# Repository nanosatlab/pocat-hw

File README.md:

# 3CatNXT PocketQube — Hardware

Hardware repository for the IEEE GRSS PocketQube built at the [NanoSat Lab (UPC)](https://nanosatlab.upc.edu/).

It holds the complete electrical and mechanical design of the satellite: KiCad projects for every
PCB in the stack, the SolidWorks/STEP assembly of the full spacecraft, the deployment mechanisms,
and the ground/mechanical support equipment used to integrate and test it.

This repository contains **design data only** — there is nothing to build or run. Flight and
ground software live elsewhere, as does the PL3 payload hardware
([nanosatlab/pocat-rfi-5g](https://github.com/nanosatlab/pocat-rfi-5g)).

---

## Repository layout

| Path | What it is |
|---|---|
| `pq_eps/` | Electrical Power Subsystem |
| `pq_obc_comms/` | On-Board Computer + COMMS transceiver |
| `pq_adcs/` | Attitude Determination and Control System |
| `pq_pl1/` | Payload 1 interface board |
| `pq_pl2/` | Payload 2 — L-band receiver |
| `pq_topboard/` | +Z face board |
| `pq_botboard/` | −Z face board |
| `pq_latboard/` | Lateral (side) face board |
| `pq_ymag_board/` | +Y magnetorquer board |
| `pq_botnotsobot/` | Deployment-switch / slider board |
| `pq_egse/` | EGSE — electrical ground support equipment breakout |
| `assembly/` | SolidWorks + STEP mechanical assembly of the whole satellite |
| `Vitrina_PQ/` | Display case (acrylic showcase) for the engineering model |

Each KiCad project directory typically contains the `.kicad_sch` / `.kicad_pcb` / `.kicad_pro`
triplet, an exported `.step` for mechanical integration, and a `production/` folder with the IPC
netlist and (where fabricated) Gerbers. Directories suffixed `_old` are superseded revisions kept
for traceability; `pq_pl2/Imports/` holds the original Altium design that PL2 was migrated from.

---

## The boards

The satellite is a stack of 40 × 40 mm boards held between structural face boards that also carry
the solar cells and thermal sensors.

### Stack boards (40 × 40 mm)

**`pq_eps` — Electrical Power Subsystem** · 4-layer, 1.6 mm

Solar energy harvesting through **SPV1040** MPPT boost converters, battery charging and
power-path management by an **LTC4040**, coulomb counting via a **DS2782** fuel gauge, and
regulated rails from an **ISL9120** buck-boost. Carries the kill-switch logic that gates the
main regulator, plus the antenna burn-wire release (`BURNCOMMS`) and per-rail enables for the
ADCS and payloads. Battery is a single Li-ion **LP14430** cell.

**`pq_obc_comms` — On-Board Computer & COMMS** · 4-layer, 1.6 mm

**STM32L476RGT6** microcontroller with a 32 MHz TCXO and a 32.768 kHz RTC crystal, paired with a
**SX1262** sub-GHz LoRa transceiver. RF front end uses a **BGS12PL6** antenna switch out to U.FL
and MS-156C test connectors. The STM32CubeMX pin configuration lives alongside the project in
`STM32L476RG_config/STM32L476RG_config.ioc`, and an interactive BOM is generated at
`pq_obc_comms/bom/ibom.html`.

**`pq_adcs` — Attitude Determination & Control** · 6-layer, 1.6 mm

Sensing from an **IIM-42652** 6-axis IMU and an **MMC5983MA** magnetometer, with sun-sensor
conditioning through **LPV542** op-amps and a **TMUX1108** analog multiplexer.

Two revisions are tracked:
- `PQ_ADCS/` — original design, magnetorquer coils driven by a **BD2606MVV**.
- `PQ_ADCS_HBridge/` — current revision, redesigned around **DRV8214** H-bridge drivers. The
  vendor-supplied symbol, footprint and STEP for the DRV8214 are vendored in
  `PQ_ADCS_HBridge/DRV8214RTER/`.

**`pq_pl2` — L-band receiver payload** · 4-layer, 1.58 mm

Full receive chain: **BFCG162W** LNA → **LEE2-6+** gain stage → **MAX2121** direct-conversion
tuner, with an **LT5537** RF power detector for level monitoring and an **LT3048** ultra-low-noise
LDO feeding the RF section. Clocked by an **ECS-TXO-2016MV** TCXO; MS-156C and U.FL connectors
provide antenna and test access.

**`pq_pl1` — Payload 1 interface** · 2-layer, 1.6 mm

Passive interface/adapter board exposing the stack connector to the PL1 experiment.

### Face and structural boards

**`pq_topboard` / `pq_botboard` / `pq_latboard`** · 2-, 6- and 6-layer respectively

These form the outer faces of the cube. They mount **SLCD-61N8** solar cells and **TCN75A**
digital temperature sensors, and route the harness into the stack. The bottom board additionally
carries **TPS7A7001/7002** LDOs, and the lateral board brings out coaxial connectors for the
deployable antenna. Face boards are 2 mm thick because they are structural.

**`pq_ymag_board`** · 6-layer, 2 mm, 45 × 45 mm

+Y magnetorquer — an air-core coil etched into the PCB, driven from the ADCS board.

**`pq_botnotsobot`** · 2-layer, 1.6 mm, 64 × 58 mm

Slider board carrying the **D2FLA** deployment/kill switches that hold the satellite inert inside
the deployer.

**`pq_egse`** · 6-layer

Electrical Ground Support Equipment. A large breakout fixture that fans every stack connector out
to 0.1" headers so subsystems can be probed, powered and stimulated individually on the bench.
Fabrication Gerbers and drill files are checked in under `pq_egse/manufacturing/`.

---

## Mechanical assembly

`assembly/` is the SolidWorks model of the integrated spacecraft. The top-level assemblies are:

- `ieee_grss_pocketqube.SLDASM` — the full satellite.
- `ieee_grss_pocketqube_beta antena.SLDASM` — variant with the deployed antenna configuration.

Supporting content is organised by subsystem — `eps/`, `adcs/`, `obc&comms/`, `payloads/`,
`structure/`, `lateral/`, `bottom/`, `slider/` — and each PCB folder carries the board as both a
`.step` and a `.SLDPRT`, together with the Edge_Cuts and silkscreen DXF/SVG exports used to keep
the mechanical model in sync with the electrical design.

Of note:

- **`assembly/lateral/antena-deployment/`** — the COMMS tape-spring antenna and its burn-wire
  release: turret, pivot, spring, clip and the resistor that cuts the restraint.
- **`assembly/Lband_Deployment_Mechanism/`** — deployment mechanism for the L-band payload
  antenna (`Lband3d_2res_v7.2.SLDASM`), with its own board and antenna sub-assemblies and a
  `STEP_files/` export set.
- **`assembly/payloads/pl3/`** — RFI-5G payload structure (antenna, supports, SMP interface).
  Mechanical only — the PL3 electrical design lives in its own repository,
  [nanosatlab/pocat-rfi-5g](https://github.com/nanosatlab/pocat-rfi-5g).
- **`assembly/MGSE_Assembly/`** — Mechanical Ground Support Equipment: the jigs and supports used
  to hold the satellite during integration.
- **`assembly/structure/`** — chassis parts plus the screw, nut and spacer library (M2/M3 ISO).

---

## Working with this repository

**Tools.** KiCad 7 or newer is required; the EPS and ADCS H-Bridge projects have been saved with a
more recent file format (`20260206`) than the rest of the stack, so opening them in an older KiCad
will fail. Mechanical files are SolidWorks, with STEP exports provided for anyone without it.

**Exports are checked in on purpose.** STEP files, Edge_Cuts/silkscreen DXFs and `production/`
netlists are tracked so that mechanical integration and manufacturing can proceed without
re-running KiCad. If you change a board outline or a connector position, re-export the STEP and
DXF and commit them in the same change — otherwise the mechanical assembly silently drifts out of
date.

**What is ignored.** `.gitignore` excludes KiCad backups, autosaves, lock files, netlists, and
generated BOM `.csv`/`.xml`. Note that it also ignores `production/` and `*-backups/` directories
by default; the ones present in the repository were committed before those rules were added and
remain tracked.

**Branching.** Work happens on per-subsystem branches (`eps_updated`, `adcs_hbridge_revision`,
`Lateral_and_bottom_connectors`, …) which are merged into `main` once the revision passes review.
Binary CAD files do not merge — coordinate before two people edit the same board.

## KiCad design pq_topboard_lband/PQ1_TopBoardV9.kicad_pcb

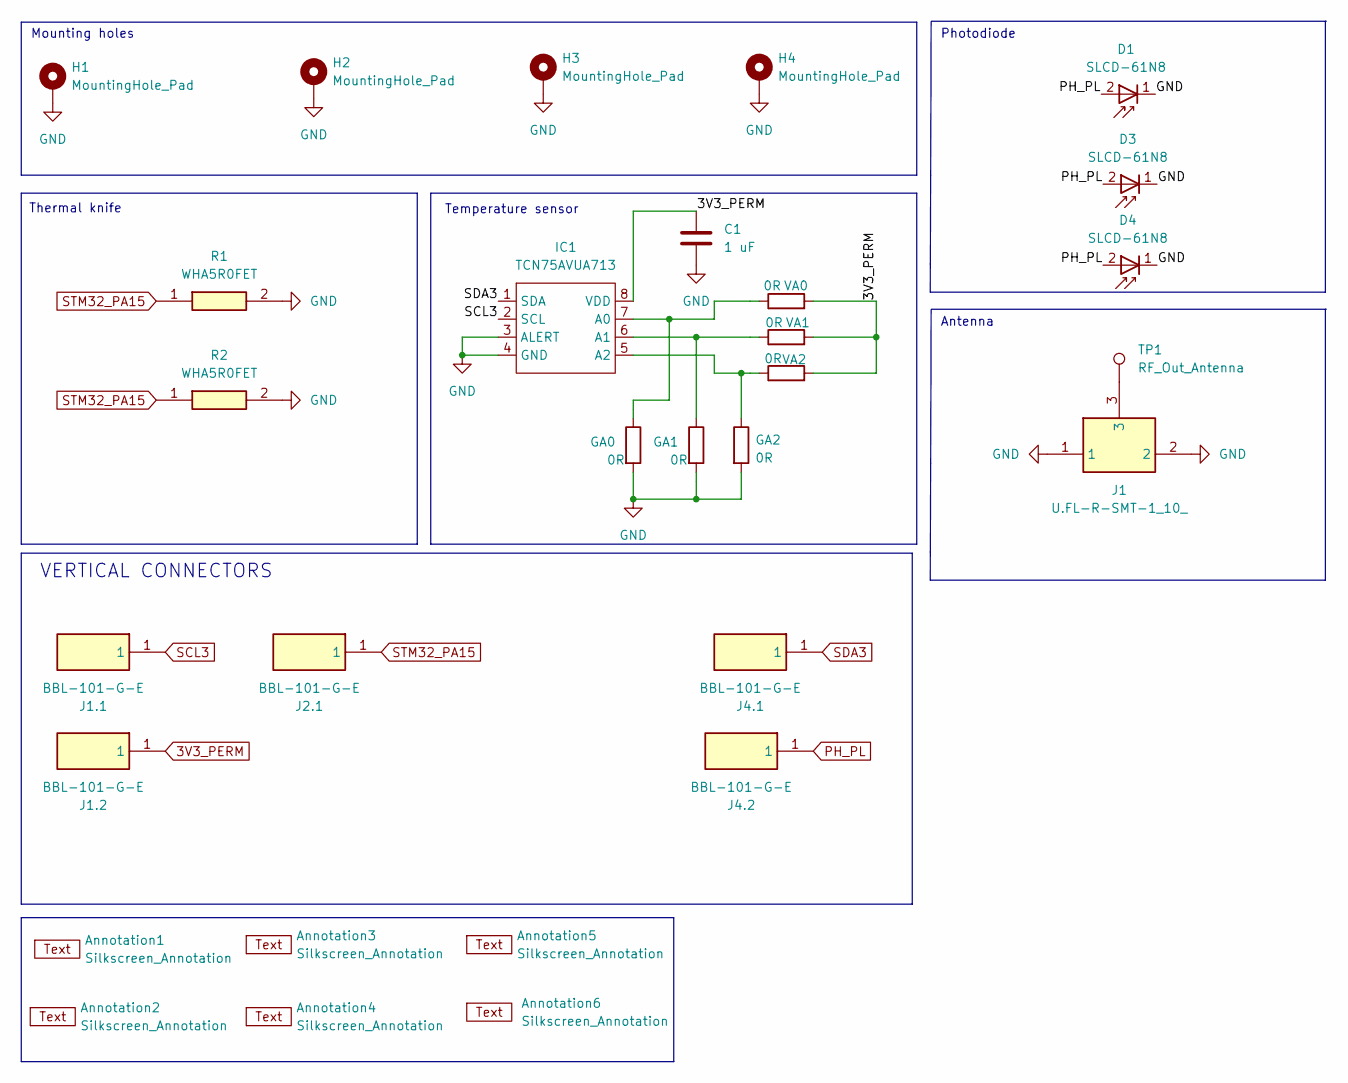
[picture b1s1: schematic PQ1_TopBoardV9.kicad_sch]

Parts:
Annotation1: Silkscreen_Annotation; IEEE_logo
Annotation2: Silkscreen_Annotation; GRSS
Annotation3: Silkscreen_Annotation; NSL_long
Annotation4: Silkscreen_Annotation; Telecos
Annotation5: Silkscreen_Annotation; UPC_positiu
Annotation6: Silkscreen_Annotation; NSL_Lektron
C1: 1 uF; C_0603_1608Metric; Manufacturer Part Numbe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 GRM188R72A104KA35J
D1, D3, D4: SLCD-61N8; Manufacturer Part Numbe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 SLCD-61N8
GA0, GA1, GA2: 0R; R_0805_2012Metric; Manufacturer Part Numbe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 CRCW08055K00JNTA
H1, H2, H3, H4: MountingHole_Pad; MountingHole_3.2mm_M3_ISO14580_Pad; Manufacturer Part Numbe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 N/A
IC1: TCN75AVUA713; TCN75AVOA; Manufacturer Part Numbe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 TCN75AVOA
J1: U.FL-R-SMT-1_10_; Mouser Part Number 798-U.FL-R-SMT-110
J1.1, J1.2, J2.1, J4.1, J4.2: BBL-101-G-E; BBL-101-Y-X; Mouser Part Number 200-BBL101GE
R1, R2: WHA5R0FET; RESAD1524W60L508D254; Mouser Part Number 588-WHA5R0FET
TP1: RF_Out_Antenna; TestPoint_Keystone_5015_Micro_Mini
VA0, VA1, VA2: 0R; R_0805_2012Metric; Manufacturer Part Numbe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 CRCW08055K00JNTA

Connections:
3V3_PERM: C1.1, IC1.8 (VDD), J1.2.1 (1_1), VA0.2, VA1.2, VA2.2
GND: C1.2, D1.1, D3.1, D4.1, GA0.2, GA1.2, GA2.2, H1.1 (1_1), H2.1 (1_1), H3.1 (1_1), H4.1 (1_1), IC1.3 (ALERT), IC1.4 (GND), J1.1, J1.2, R1.2, R2.2
unnamed: GA0.1, IC1.7 (A0), VA0.1
unnamed: GA1.1, IC1.6 (A1), VA1.1
unnamed: GA2.1, IC1.5 (A2), VA2.1
unnamed: J1.3, TP1.1 (1_1)
PH_PL: D1.2, D3.2, D4.2, J4.2.1 (1_1)
SCL3: IC1.2 (SCL), J1.1.1 (1_1)
SDA3: IC1.1 (SDA), J4.1.1 (1_1)
STM32_PA15: J2.1.1 (1_1), R1.1, R2.1

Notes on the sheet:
Photodiode
VERTICAL CONNECTORS
Thermal knife
Mounting holes
Antenna
Temperature sensor

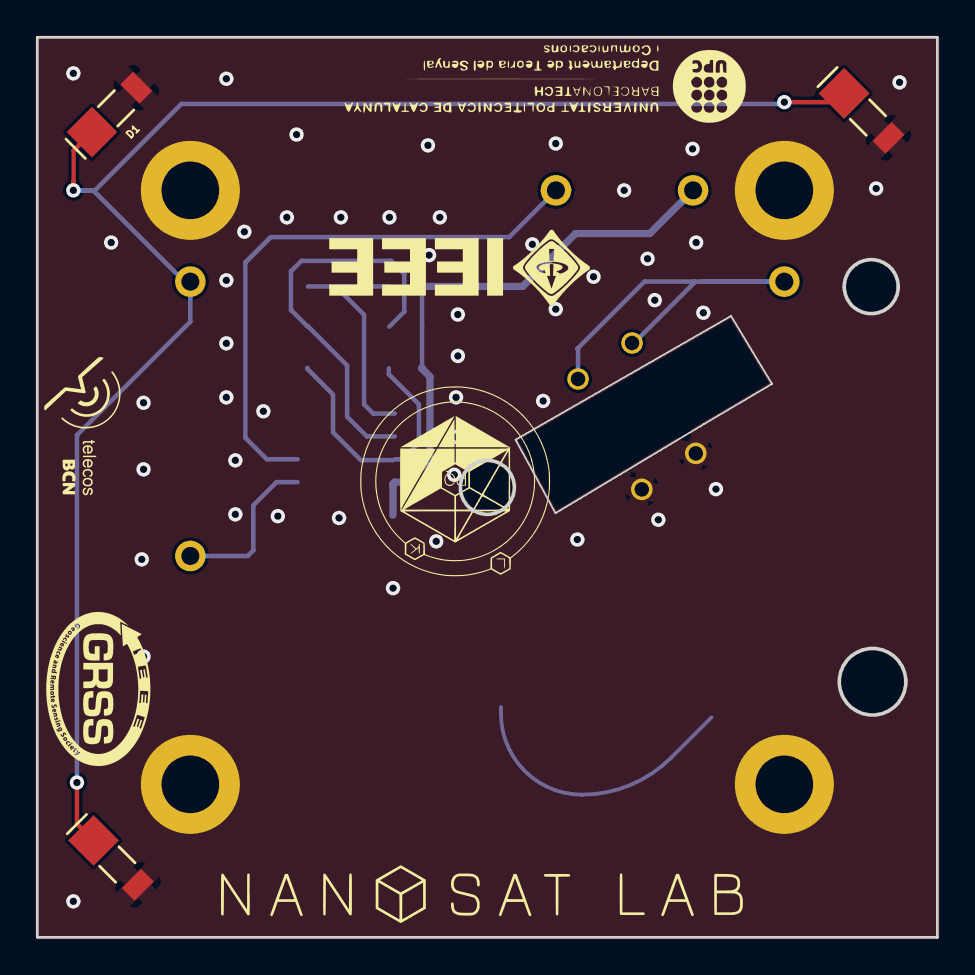
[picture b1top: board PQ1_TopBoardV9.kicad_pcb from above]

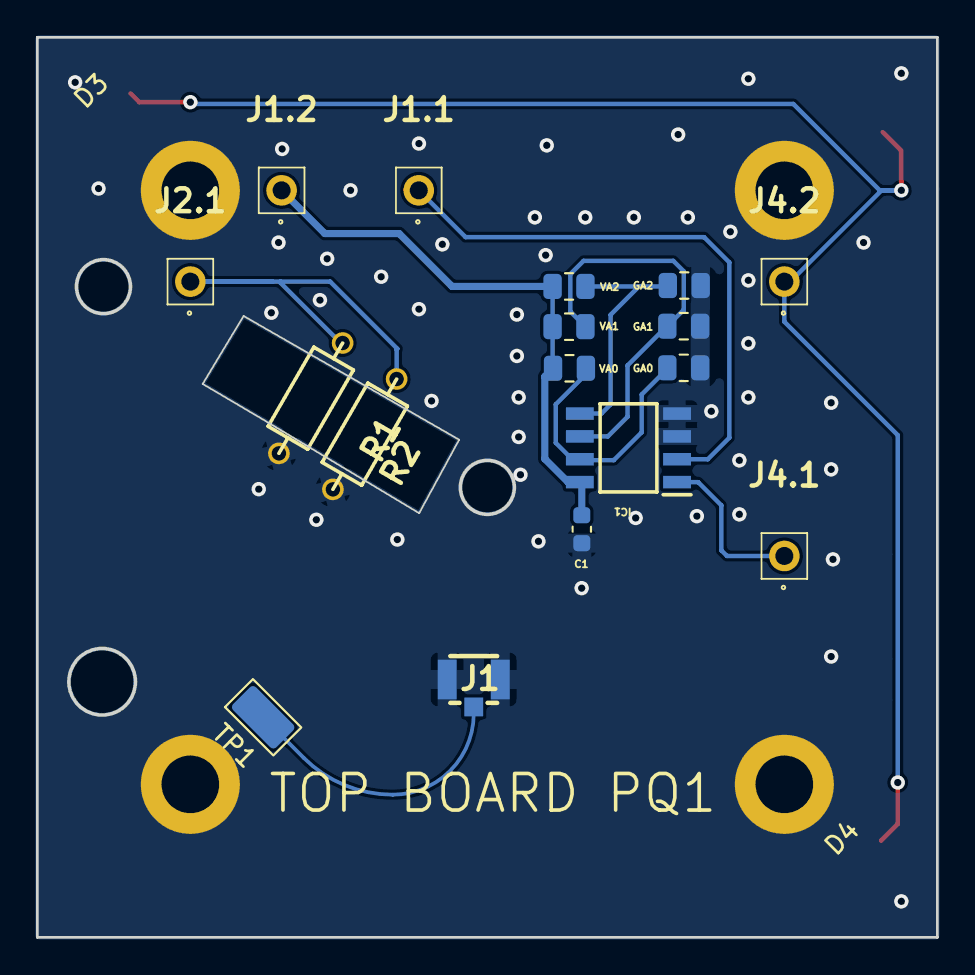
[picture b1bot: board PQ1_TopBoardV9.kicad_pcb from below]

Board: 2 copper layers, 50.0 x 50.0 mm, 30 parts (17 on the bottom side), 10 nets.

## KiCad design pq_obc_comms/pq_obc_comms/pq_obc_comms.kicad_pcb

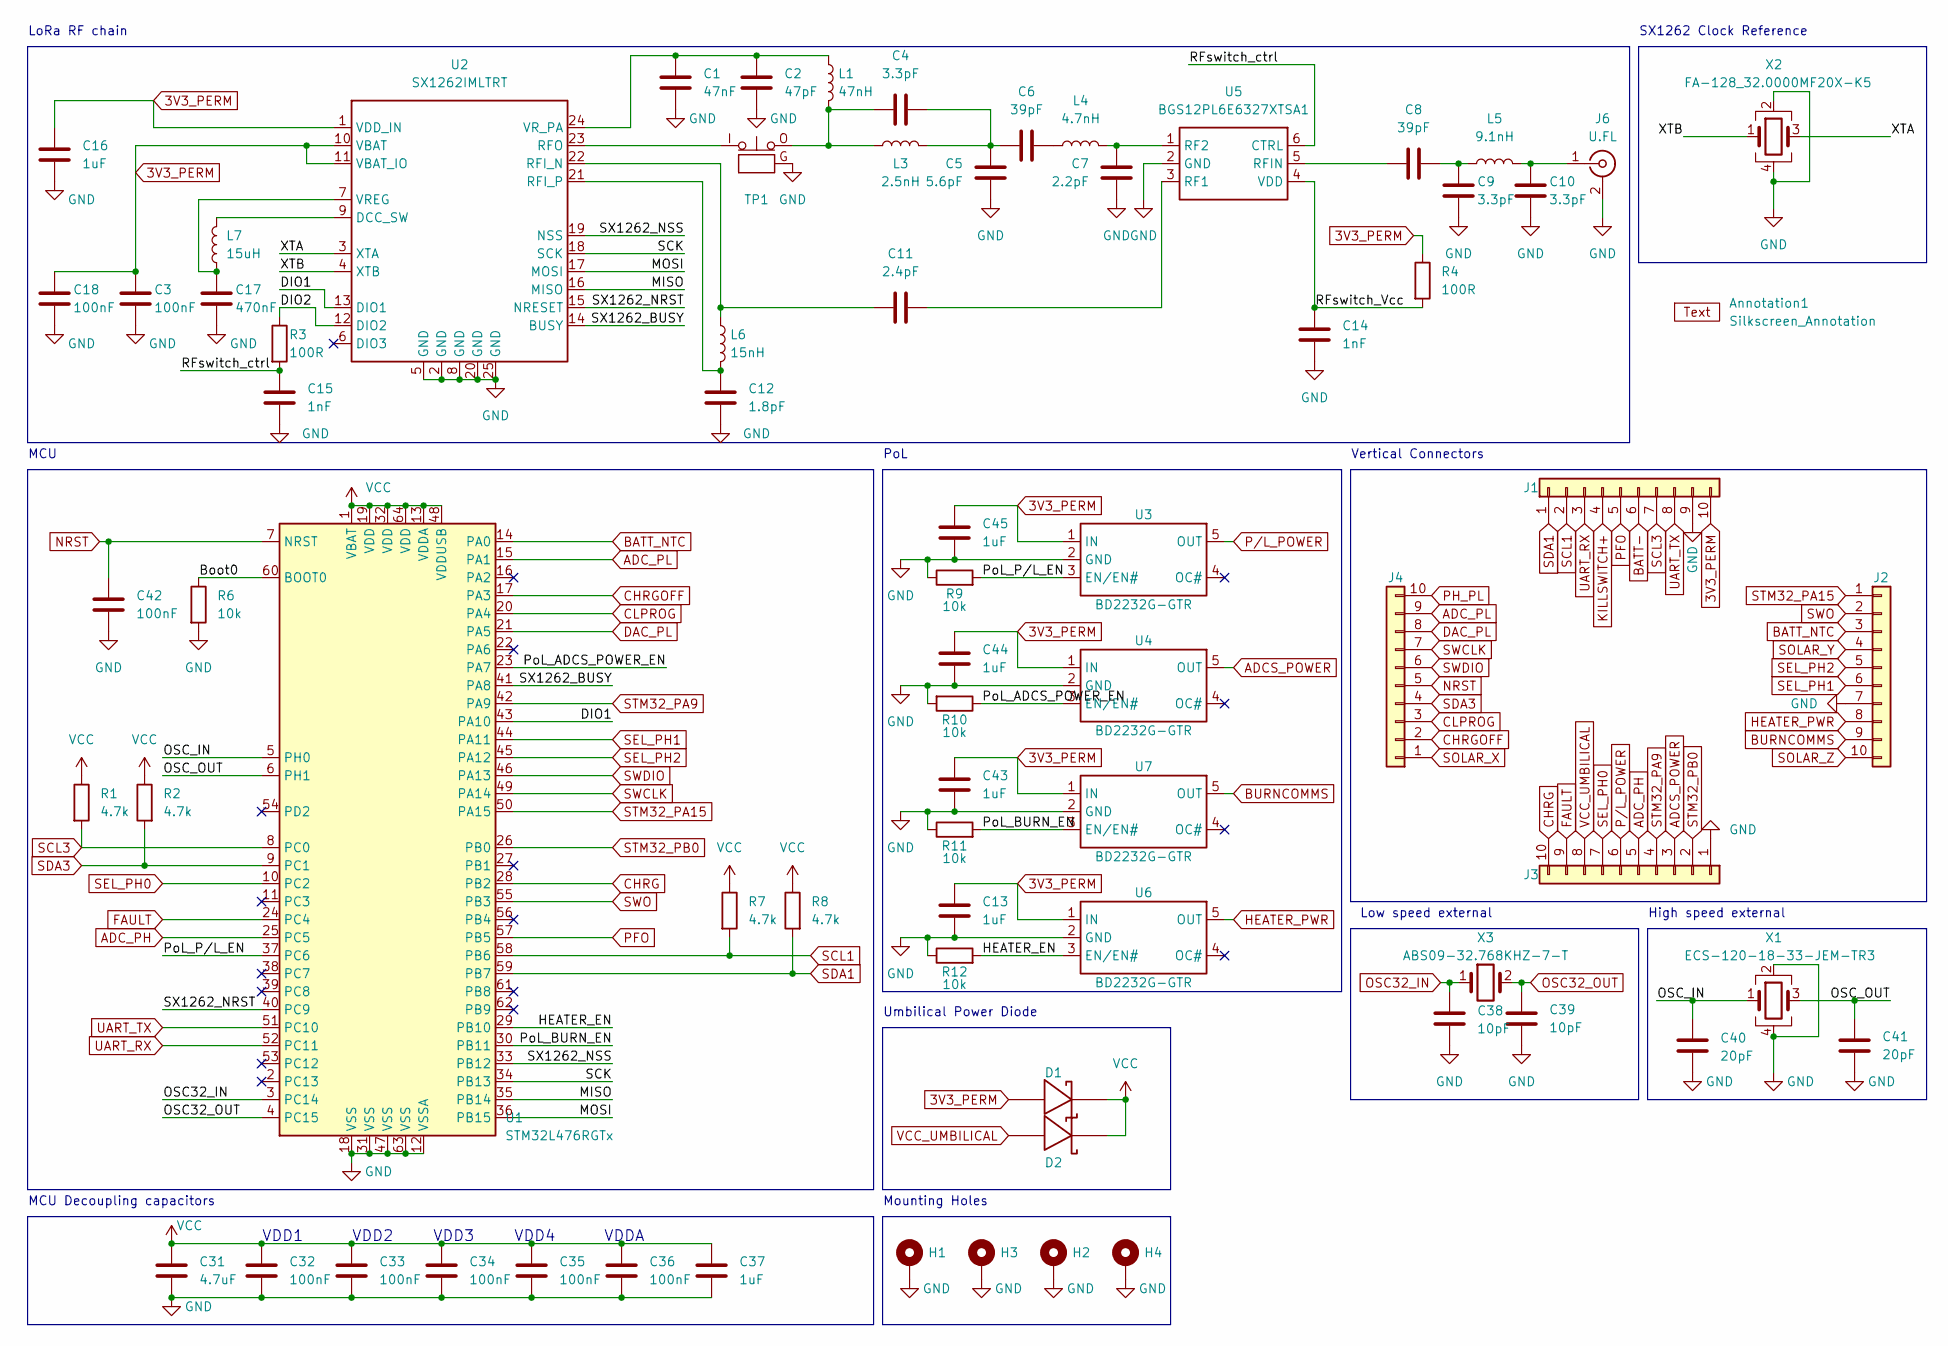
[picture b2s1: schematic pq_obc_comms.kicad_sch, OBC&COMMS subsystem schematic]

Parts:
Annotation1: Silkscreen_Annotation; Bike
C1: 47nF; C_0402_1005Metric; Manufacturer Part Numbe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 GRM155R71C473KA01J
C2: 47pF; C_0402_1005Metric; Manufacturer Part Numbe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 GJM1555C1H470JB01J
C3, C18, C32, C33, C34, C35, C36, C42: 100nF; C_0603_1608Metric; Manufacturer Part Numbe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 GRM188R72A104KA35J
C4, C9, C10: 3.3pF; C_0402_1005Metric; Manufacturer Part Numbe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 600L3R3BT200T
C5: 5.6pF; C_0402_1005Metric; Manufacturer Part Numbe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 600L5R6BTN200T
C6, C8: 39pF; C_0402_1005Metric; Manufacturer Part Numbe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 GJM1555C1H390FB01D
C7: 2.2pF; C_0402_1005Metric; Manufacturer Part Numbe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 600L2R2BT200T
C11: 2.4pF; C_0402_1005Metric; Manufacturer Part Numbe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 600L2R4BW200T
C12: 1.8pF; C_0402_1005Metric; Manufacturer Part Numbe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 600L1R8BW200T
C13, C16, C37, C43, C44, C45: 1uF; C_0603_1608Metric; Manufacturer Part Numbe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 GRM188R61A105KA61D
C14, C15: 1nF; C_0603_1608Metric; Manufacturer Part Numbe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 0603B102K500CT
C17: 470nF; C_0603_1608Metric; Manufacturer Part Numbe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 GRM188R7YA474KE05D
C31: 4.7uF; C_0603_1608Metric; Manufacturer Part Numbe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 GRT188R61E475KE13D
C38, C39: 10pF; C_0603_1608Metric; Manufacturer Part Numbe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 06035A100GAT2A
C40, C41: 20pF; C_0603_1608Metric; Manufacturer Part Numbe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 GCM1885C2A200JA16D
D1, D2: type="D" model="RBS1LAM40ATR" lib=""; RBS1LAM40ATR_Schottky; Manufacturer Part Numbe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 RBS1LAM40ATR
H1, H2, H3, H4: MountingHole_Pad; MountingHole_3.2mm_M3_Pad
J1, J2, J3, J4: Conn_01x10; SLW-110-01; Manufacturer Part Numbe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 CES-110-01-T-S
J6: U.FL; U.FL_Hirose_U.FL-R-SMT-1_Vertical; Manufacturer Part Numbe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 U.FL-R-SMT-1(10)
L1: 47nH; L_0402_1005Metric; Manufacturer Part Numbe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 0402DC-47NXGRW
L3: 2.5nH; L_0402_1005Metric; Manufacturer Part Numbe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 LQW15AN2N5B00D
L4: 4.7nH; L_0402_1005Metric; Manufacturer Part Numbe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 0402DC-4N7XGRW
L5: 9.1nH; L_0402_1005Metric; Manufacturer Part Numbe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 LQW15AN9N1G8ZD
L6: 15nH; L_0402_1005Metric; Manufacturer Part Numbe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 LQW15AN15NH00D
L7: 15uH; L_0805_2012Metric; Manufacturer Part Numbe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 LQM21DN150M70L
R1, R2, R7, R8: 4.7k; R_0603_1608Metric; Manufacturer Part Numbe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 CRCW06034K70JNEAC
R3, R4: 100R; R_0603_1608Metric; Manufacturer Part Numbe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 RC0603JR-07100RL
R6, R9, R10, R11, R12: 10k; R_0402_1005Metric; Manufacturer Part Numbe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 CRCW040220K0FKEDC
TP1: CoaxialSwitch_Testpoint; CoaxialSwitch_Hirose_MS-156C3_Horizontal; Manufacturer Part Numbe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 MS-156C3(20)
U1: STM32L476RGTx; LQFP-64_10x10mm_P0.5mm; Manufacturer Part Numbe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 STM32L476RGT6
U2: SX1262IMLTRT; QFN-24-1EP_4x4mm_P0.5mm_EP2.6x2.6mm; Manufacturer Part Numbe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 SX1262IMLTRT
U3, U4, U6, U7: BD2232G-GTR; SOT-23-5; Manufacturer Part Numbe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 BD2232G-GTR
U5: BGS12PL6E6327XTSA1; PG-TSLP-6-4; Manufacturer Part Numbe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 BGS12PL6E6327XTSA1
X1: ECS-120-18-33-JEM-TR3; ECS-120-18-33; Manufacturer Part Numbe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 ECS-120-18-33-JEM-TR3
X2: FA-128_32.0000MF20X-K5; EPSON_FA128; Manufacturer Part Numbe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 FA-128 32.0000MF20X-K5
X3: ABS09-32.768KHZ-7-T; ABS09; Manufacturer Part Numbe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 ABS09-32.768KHZ-7-T

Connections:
3V3_PERM: C3.1, C13.1, C16.1, C18.1, C43.1, C44.1, C45.2, D1.2, J1.10, R4.1, U2.1 (VDD_IN), U2.10 (VBAT), U2.11 (VBAT_IO), U3.1 (IN), U4.1 (IN), U6.1 (IN), U7.1 (IN)
/Boot0: R6.1, U1.60 (BOOT0)
/DIO1: U1.43 (PA10), U2.13 (DIO1)
/DIO2: R3.1, U2.12 (DIO2)
/HEATER_EN: R12.2, U1.29 (PB10), U6.3 (EN/EN#)
/MISO: U1.35 (PB14), U2.16 (MISO)
/MOSI: U1.36 (PB15), U2.17 (MOSI)
/OSC_IN: C40.1, U1.5 (PH0), X1.1
/OSC_OUT: C41.1, U1.6 (PH1), X1.3
/PoL_ADCS_POWER_EN: R10.1, U1.23 (PA7), U4.3 (EN/EN#)
/PoL_BURN_EN: R11.2, U1.30 (PB11), U7.3 (EN/EN#)
/PoL_P/L_EN: R9.2, U1.37 (PC6), U3.3 (EN/EN#)
/RFswitch_Vcc: C14.1, R4.2, U5.4 (VDD)
/RFswitch_ctrl: C15.1, R3.2, U5.6 (CTRL)
/SCK: U1.34 (PB13), U2.18 (SCK)
/SX1262_BUSY: U1.41 (PA8), U2.14 (BUSY)
/SX1262_NRST: U1.40 (PC9), U2.15 (NRESET)
/SX1262_NSS: U1.33 (PB12), U2.19 (NSS)
/XTA: U2.3 (XTA), X2.3
/XTB: U2.4 (XTB), X2.1
ADCS_POWER: J3.3, U4.5 (OUT)
ADC_PH: J3.5, U1.25 (PC5)
ADC_PL: J4.9, U1.15 (PA1)
BATT-: J1.6
BATT_NTC: J2.3, U1.14 (PA0)
BURNCOMMS: J2.9, U7.5 (OUT)
CHRG: J3.10, U1.28 (PB2)
CHRGOFF: J4.2, U1.17 (PA3)
CLPROG: J4.3, U1.20 (PA4)
DAC_PL: J4.8, U1.21 (PA5)
FAULT: J3.9, U1.24 (PC4)
GND: C1.2, C2.2, C3.2, C5.2, C7.2, C9.2, C10.2, C12.2, C13.2, C14.2, C15.2, C16.2, C17.2, C18.2, C31.2, C32.2, C33.2, C34.2, C35.2, C36.2, C37.2, C38.2, C39.2, C40.2, C41.2, C42.2, C43.2, C44.2, C45.1, H1.1 (1_1), H2.1 (1_1), H3.1 (1_1), H4.1 (1_1), J1.9, J2.7, J3.1, J6.2 (Ext), R6.2, R9.1, R10.2, R11.1, R12.1, TP1.G, U1.12 (VSSA), U1.18 (VSS), U1.31 (VSS), U1.47 (VSS), U1.63 (VSS), U2.2 (GND), U2.5 (GND), U2.8 (GND), U2.20 (GND), U2.25 (GND), U3.2 (GND), U4.2 (GND), U5.2 (GND), U6.2 (GND), U7.2 (GND), X1.2, X1.4, X2.2, X2.4
HEATER_PWR: J2.8, U6.5 (OUT)
KILLSWITCH+: J1.4
NRST: C42.1, J4.5, U1.7 (NRST)
unnamed: C4.1, L1.2, L3.1, TP1.O
unnamed: C4.2, C5.1, C6.1, L3.2
unnamed: C6.2, L4.1
unnamed: C8.2, C9.1, L5.1
unnamed: C10.1, J6.1 (In), L5.2
unnamed: L7.2, U2.9 (DCC_SW)
unnamed: C11.1, L6.1, U2.22 (RFI_N)
unnamed: C12.1, L6.2, U2.21 (RFI_P)
unnamed: TP1.I, U2.23 (RFO)
unnamed: C17.1, L7.1, U2.7 (VREG)
unnamed: C1.1, C2.1, L1.1, U2.24 (VR_PA)
unnamed: C11.2, U5.3 (RF1)
unnamed: C7.1, L4.2, U5.1 (RF2)
unnamed: C8.1, U5.5 (RFIN)
OSC32_IN: C38.1, U1.3 (PC14), X3.1
OSC32_OUT: C39.1, U1.4 (PC15), X3.2
PFO: J1.5, U1.57 (PB5)
PH_PL: J4.10
SCL1: J1.2, R7.2, U1.58 (PB6)
SCL3: J1.7, R1.2, U1.8 (PC0)
SDA1: J1.1, R8.2, U1.59 (PB7)
SDA3: J4.4, R2.2, U1.9 (PC1)
SEL_PH0: J3.7, U1.10 (PC2)
SEL_PH1: J2.6, U1.44 (PA11)
SEL_PH2: J2.5, U1.45 (PA12)
SOLAR_X: J4.1
SOLAR_Y: J2.4
SOLAR_Z: J2.10
STM32_PA9: J3.4, U1.42 (PA9)
STM32_PA15: J2.1, U1.50 (PA15)
STM32_PB0: J3.2, U1.26 (PB0)
SWCLK: J4.7, U1.49 (PA14)
SWDIO: J4.6, U1.46 (PA13)
SWO: J2.2, U1.55 (PB3)
UART_RX: J1.3, U1.52 (PC11)
UART_TX: J1.8, U1.51 (PC10)
VCC: C31.1, C32.1, C33.1, C34.1, C35.1, C36.1, C37.1, D1.1, D2.1, R1.1, R2.1, R7.1, R8.1, U1.1 (VBAT), U1.13 (VDDA), U1.19 (VDD), U1.32 (VDD), U1.48 (VDDUSB), U1.64 (VDD)
VCC_UMBILICAL: D2.2, J3.8

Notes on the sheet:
VDD2
MCU Decoupling capacitors
LoRa RF chain
SX1262 Clock Reference
Umbilical Power Diode
VDD1
Low speed external
Vertical Connectors
MCU
VDD3
VDDA
High speed external
Mounting Holes
VDD4
PoL

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
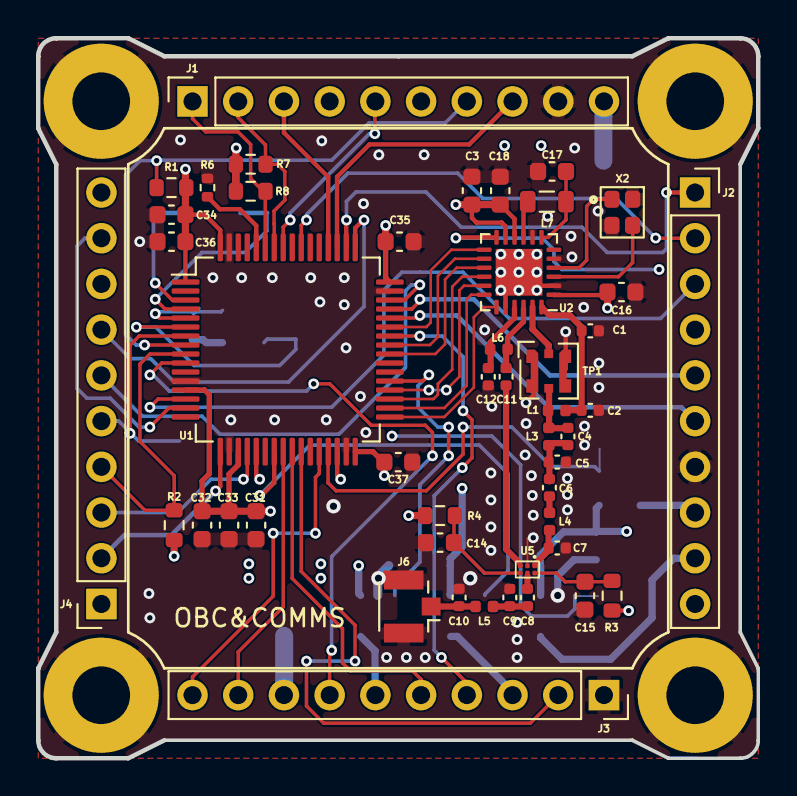
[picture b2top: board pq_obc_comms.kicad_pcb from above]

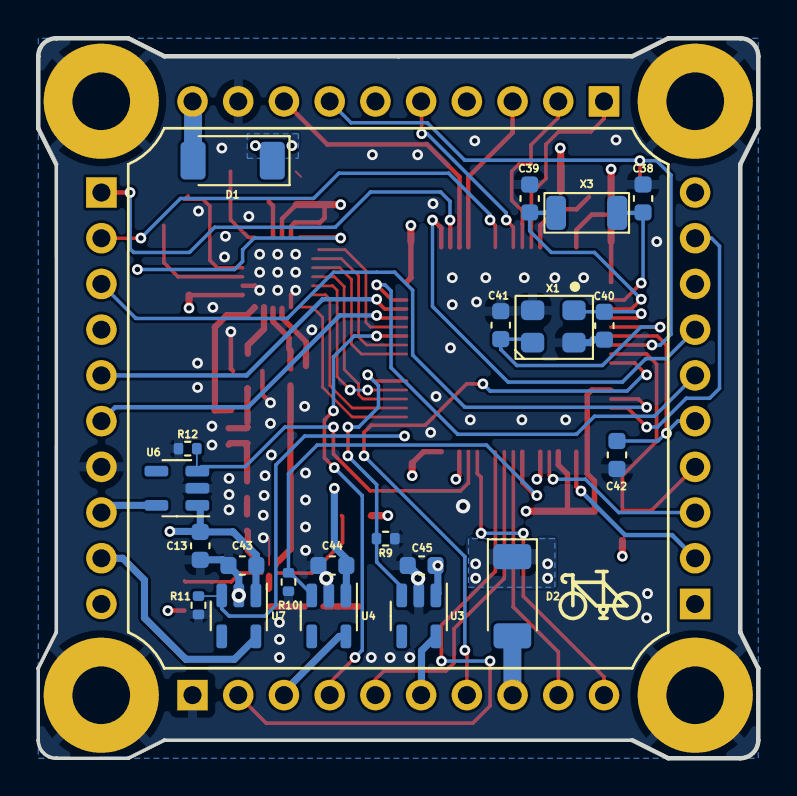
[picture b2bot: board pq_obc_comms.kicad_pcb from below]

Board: 4 copper layers, 40.0 x 40.0 mm, 73 parts (22 on the bottom side), 68 nets.

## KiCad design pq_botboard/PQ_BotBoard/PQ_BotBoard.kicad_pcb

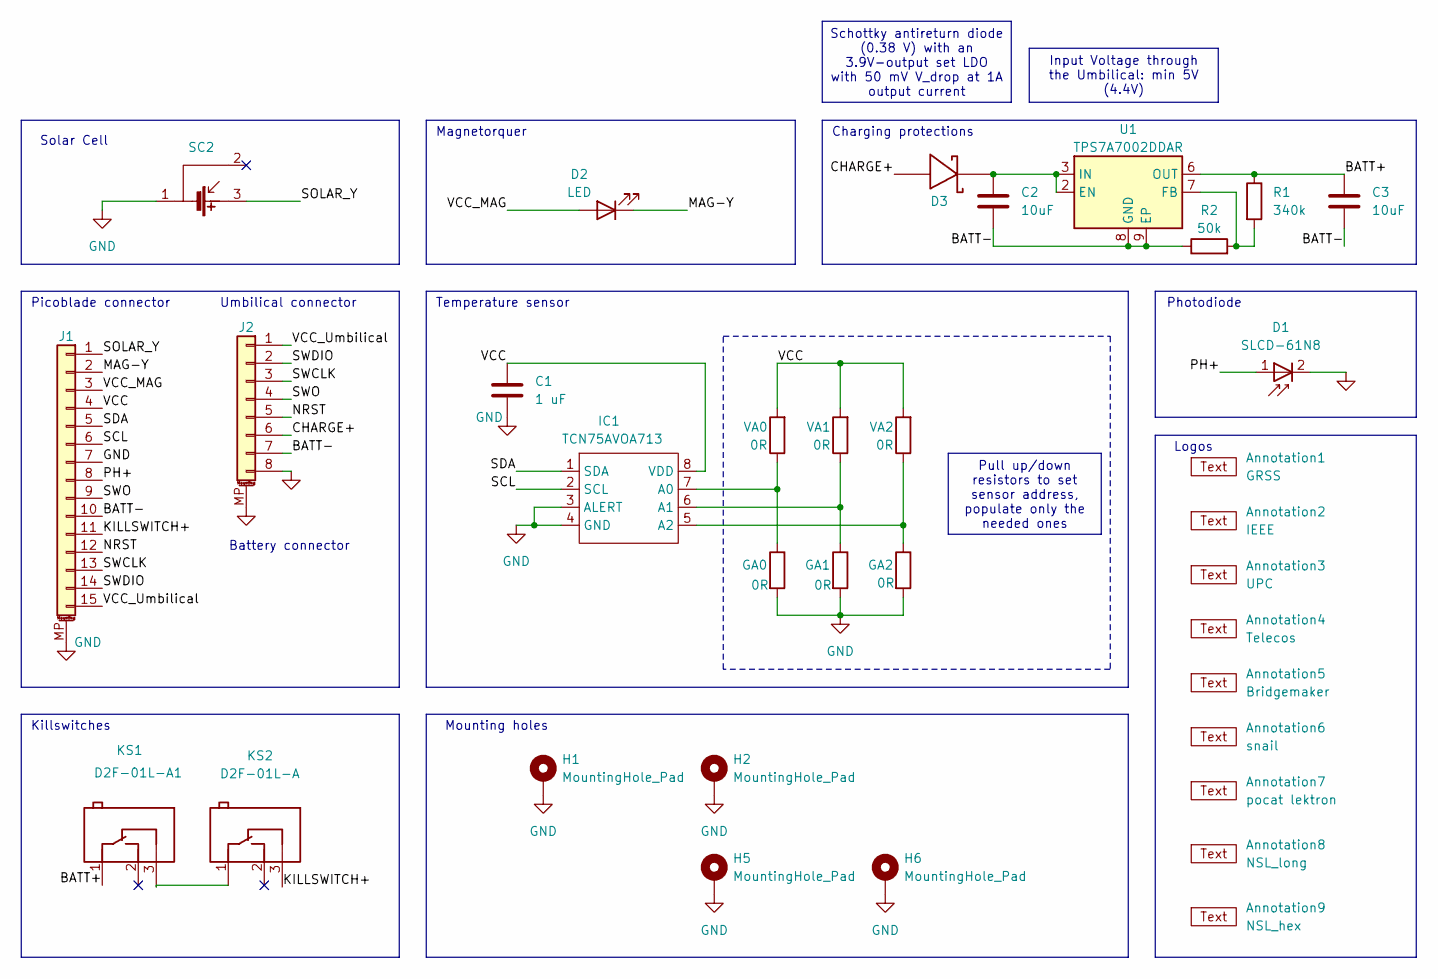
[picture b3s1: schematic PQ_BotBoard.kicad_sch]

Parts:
Annotation1: GRSS
Annotation2: IEEE; IEEE_logo
Annotation3: UPC; UPC_positiu
Annotation4: Telecos
Annotation5: Bridgemaker
Annotation6: snail; Snail
Annotation7: pocat lektron; pocat-lektron
Annotation8: NSL_long; NSL-small
Annotation9: NSL_hex; NSL_hexagon
C1: 1 uF; C_0603_1608Metric; Manufacturer Part Numbe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 GRM188R72A104KA35J
C2, C3: 10uF; C_0603_1608Metric
D1: SLCD-61N8; Manufacturer Part Numbe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 SLCD-61N8
D2: LED; LED_0402_1005Metric
D3: RBS1LAM40ATR_Schottky
GA0, GA1, GA2: 0R; R_0805_2012Metric; Manufacturer Part Numbe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 CRCW08055K00JNTA
H1, H2, H5, H6: MountingHole_Pad; MountingHole_2.2mm_M2_Pad; Manufacturer Part Numbe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 N/A
IC1: TCN75AVOA713; TCN75AVOA; Manufacturer Part Numbe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 TCN75AVOA
J1: 53261-1471; Molex_PicoBlade_53261-1571_1x15-1MP_P1.25mm_Horizontal; Manufacturer Part Numbe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 PicoBlade_53261-1571
J2: Conn_01x08_MountingPin; Molex_PicoBlade_53398-0871_1x08-1MP_P1.25mm_Vertical; Manufacturer Part Numbe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 PicoBlade_53398-0871
KS1: D2F-01L-A1; D2FLA1; Manufacturer Part Numbe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 D2F-01L
KS2: D2F-01L-A; D2FLA; Manufacturer Part Numbe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 D2F-01L-A
R1: 340k; R_0603_1608Metric
R2: 50k; R_0603_1608Metric
SC2: Lighttricity_S3040_CIC
U1: TPS7A7002DDAR; TI_SO-PowerPAD-8
VA0, VA1, VA2: 0R; R_0805_2012Metric; Manufacturer Part Numbe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 CRCW08055K00JNTA

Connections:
/BATT+: C3.1, KS1.1 (COM), R1.1, U1.6 (OUT)
/BATT-: C2.2, C3.2, J1.10, J2.7, R2.1, U1.8 (GND), U1.9 (EP)
/CHARGE+: D3.2, J2.6
/KILLSWITCH+: J1.11, KS2.3 (NC)
/MAG-Y: D2.1 (K), J1.2
/NRST: J1.12, J2.5
/PH+: D1.1, J1.8
/SCL: IC1.2 (SCL), J1.6
/SDA: IC1.1 (SDA), J1.5
/SOLAR_Y: J1.1, SC2.3
/SWCLK: J1.13, J2.3
/SWDIO: J1.14, J2.2
/SWO: J1.9, J2.4
/VCC: C1.1, IC1.8 (VDD), J1.4, VA0.2, VA1.2, VA2.2
/VCC_MAG: D2.2 (A), J1.3
/VCC_Umbilical: J1.15, J2.1
GND: C1.2, D1.2, GA0.2, GA1.2, GA2.2, H1.1, H2.1, H5.1, H6.1, IC1.3 (ALERT), IC1.4 (GND), J1.7, J1.MP (MountPin), J2.8, J2.MP (MountPin), SC2.1
unnamed: GA0.1, IC1.7 (A0), VA0.1
unnamed: GA1.1, IC1.6 (A1), VA1.1
unnamed: GA2.1, IC1.5 (A2), VA2.1
unnamed: KS1.3 (NC), KS2.1 (COM)
unnamed: C2.1, D3.1, U1.2 (EN), U1.3 (IN)
unnamed: R1.2, R2.2, U1.7 (FB)

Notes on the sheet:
Temperature sensor
Killswitches
Mounting holes
Solar Cell
Magnetorquer
Charging protections
Photodiode
Umbilical connector
Battery connector
Picoblade connector
Logos
Input Voltage through the Umbilical: min 5V (4.4V)
Schottky antireturn diode (0.38 V) with an 3.9V-output set LDO with 50 mV V_drop at 1A output current
Pull up/down resistors to set sensor address, populate only the needed ones

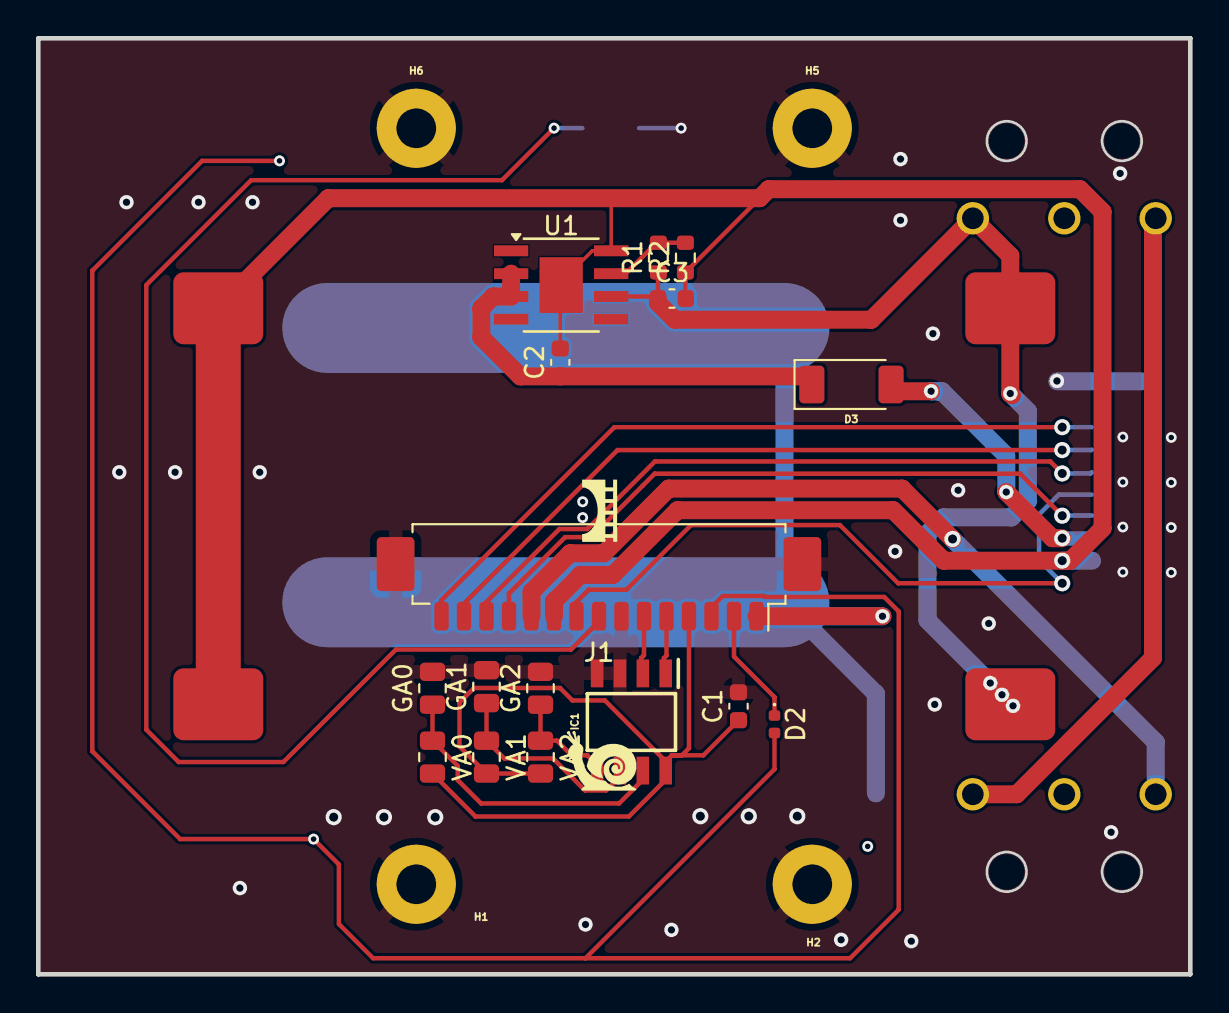
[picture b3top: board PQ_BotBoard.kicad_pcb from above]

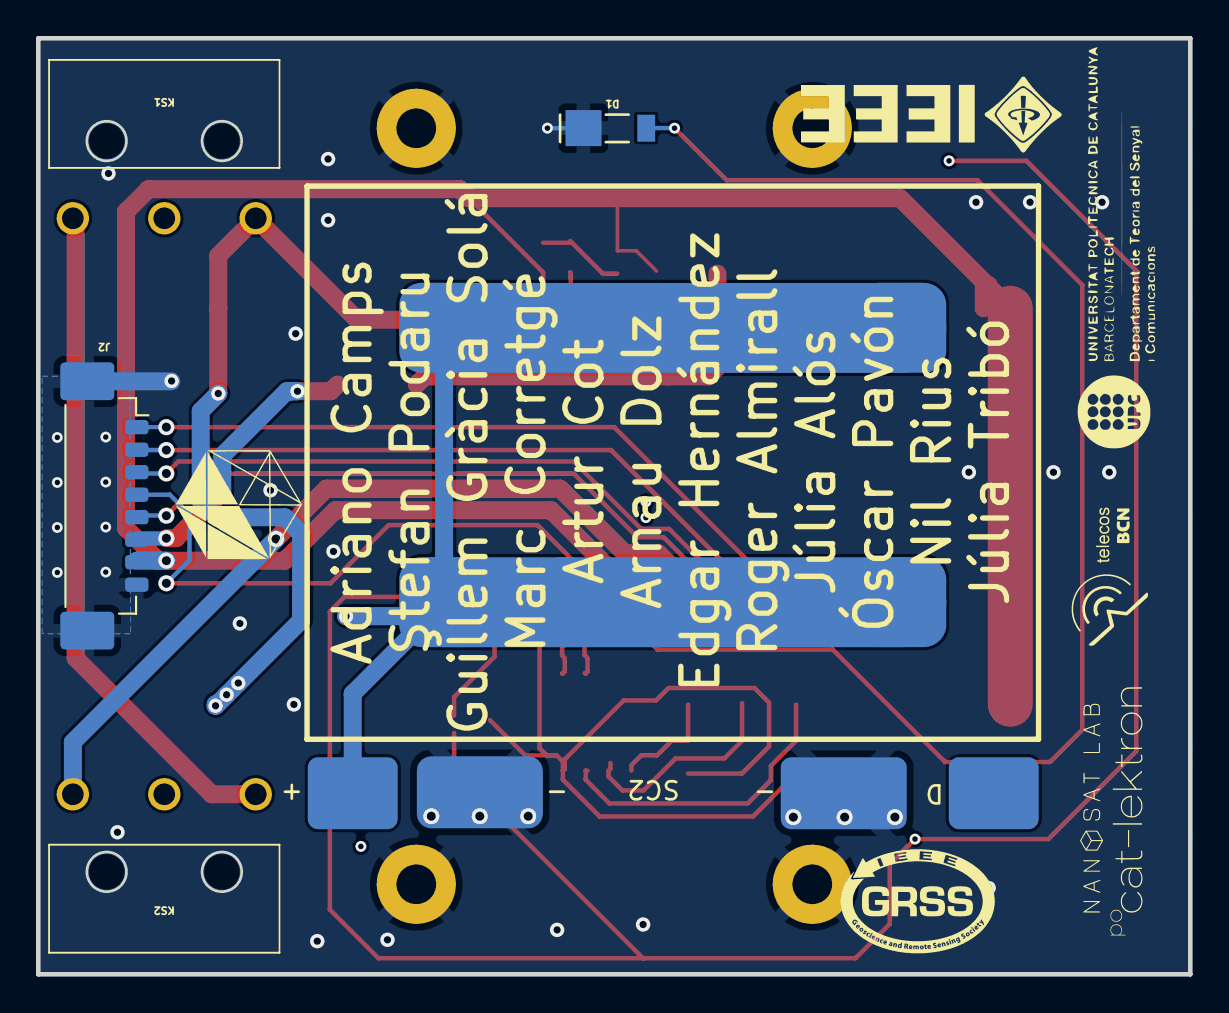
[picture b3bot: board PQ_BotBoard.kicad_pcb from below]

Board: 6 copper layers, 64.0 x 52.0 mm, 34 parts (12 on the bottom side), 23 nets.
